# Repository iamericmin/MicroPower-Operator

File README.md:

# MicroPower-Operator
A simple SAMD21 dev board

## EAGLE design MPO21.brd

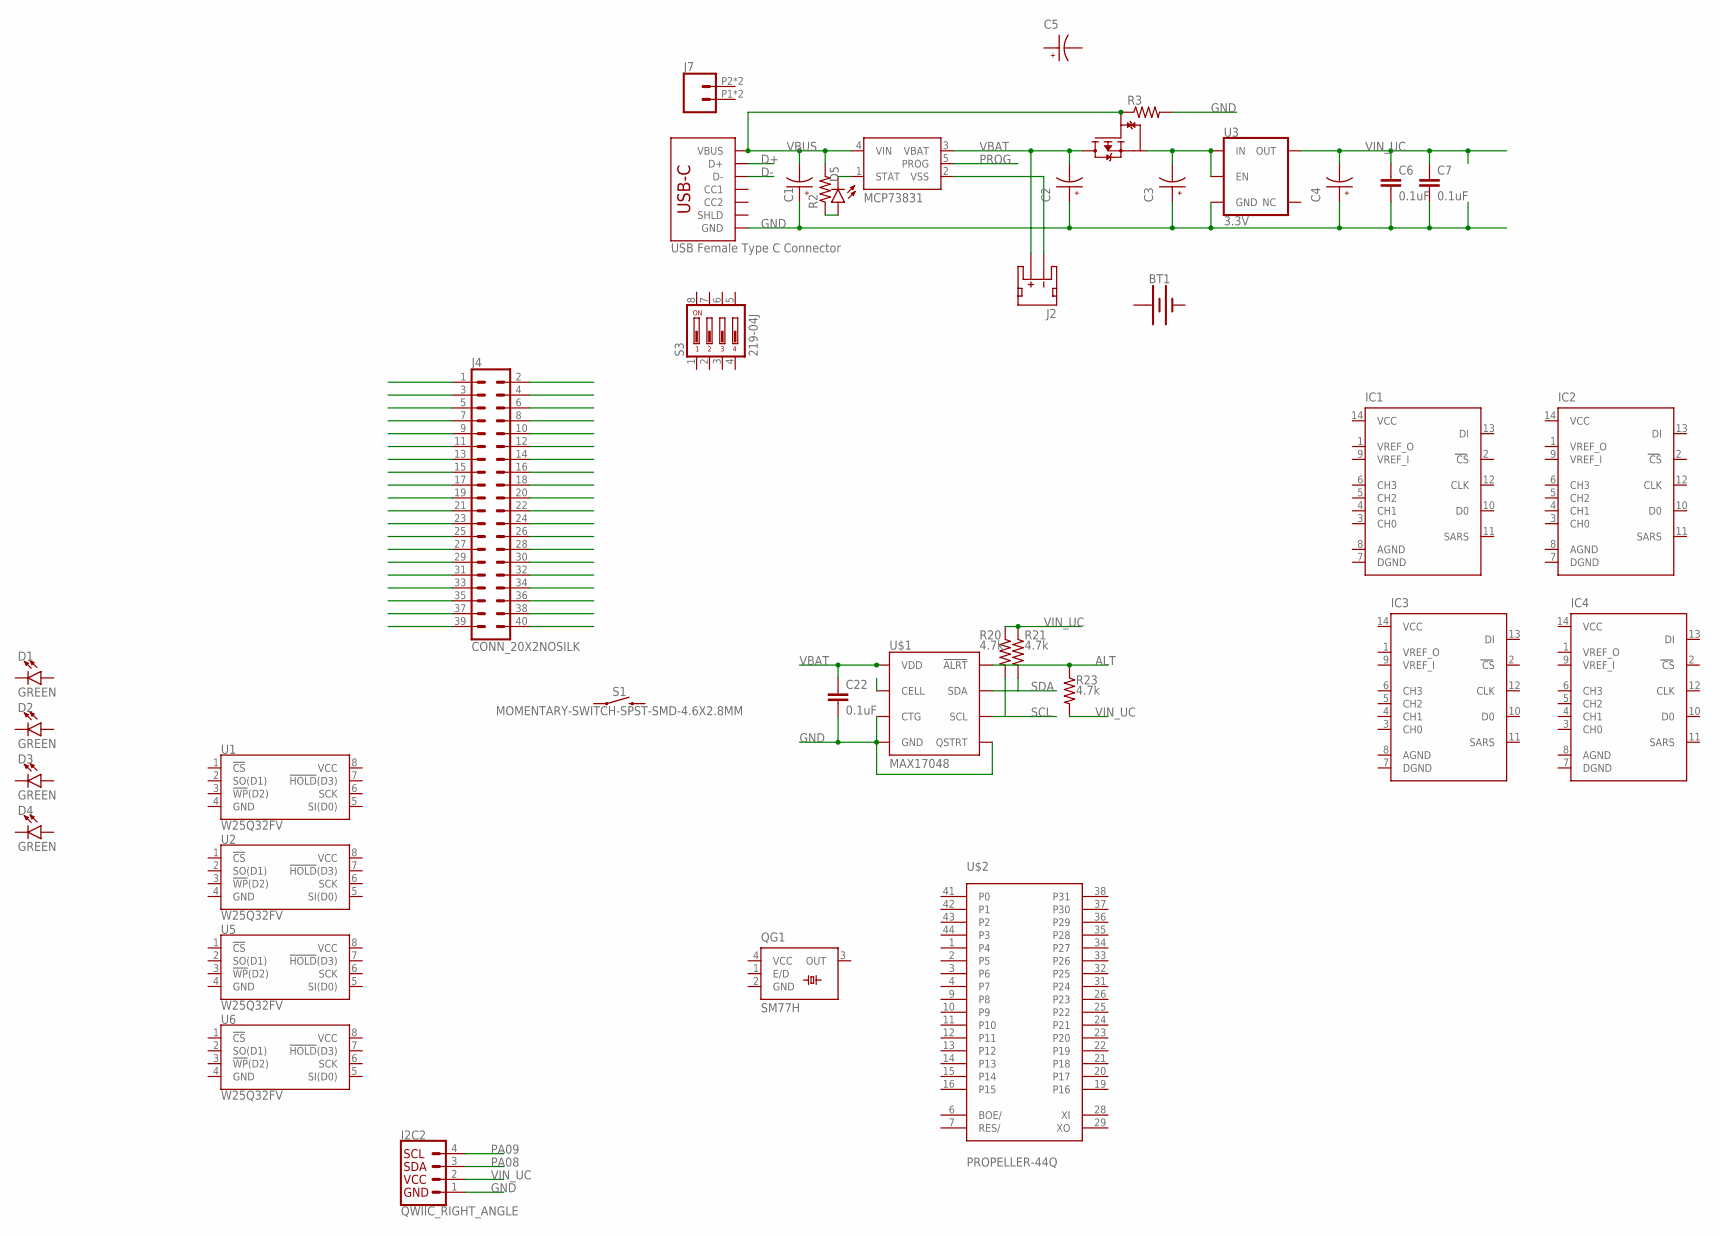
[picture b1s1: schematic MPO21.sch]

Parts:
BT1: BATTERY-20MM_SMD_4LEGS_OVERPASTE_INNER; BATTCON_20MM_4LEGS_OVERPASTE_INNER
C1, C2, C3, C4, C5: EEEFC1H1R0R; CAP_EEEFC1H1R0R
C6, C7, C22: 0.1uF; C0603
D1, D2, D3, D4, D5: GREEN; LED-1206
I2C2: QWIIC_RIGHT_ANGLE; JST04_1MM_RA
IC1, IC2, IC3, IC4: ADC08034D; SO14
J2: JST_2MM_MALE; JST-2-SMD
J4: CONN_20X2NOSILK; 2X20_NOSILK
J7: CONN_02SMALL_POKEHOME; 1X02_POKEHOME
J9: USB Female Type C Connector; USB-C-16P-4LAYER-ISOLATED
Q1: DMP1045U; SOT91P240X110-3N
QG1: SM77H
R2, R3: R-US_R0603; R0603
R20, R21, R23: 4.7k; R0603
S1: MOMENTARY-SWITCH-SPST-SMD-4.6X2.8MM; TACTILE_SWITCH_SMD_4.6X2.8MM
S3: 219-04J; CTS-219-04J
U1, U2, U5, U6: W25Q32FV; SOIC-8
U3: 3.3V; SOT23-5
U4: MCP73831; SOT23-5
U$1: MAX17048; DFN-8
U$2: PROPELLER-44Q; Q44

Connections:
+: BT1.1 (+)
-: BT1.2 (-)
AGND: IC1.8 (AGND), IC2.8 (AGND), IC3.8 (AGND), IC4.8 (AGND)
ALT: R23.1, U$1.P$5 (!ALRT)
D+: J9.A6 (D+), J9.B6 (D+)
D-: J9.A7 (D-), J9.B7 (D-)
DGND: IC1.7 (DGND), IC2.7 (DGND), IC3.7 (DGND), IC4.7 (DGND)
GND: C1.1, C2.1, C3.1, C4.1, C6.2, C7.2, C22.2, I2C2.1, J9.GND, J9.GND2 (GND), QG1.2 (GND), R3.2, U3.2 (GND), U$1.P$1 (CTG), U$1.P$4 (GND), U$1.P$6 (QSTRT), U$1.P$9 (GND)
unnamed: C3.2, Q1.2 (S), U3.1 (IN), U3.3 (EN)
unnamed: D5.C, U4.1 (STAT)
unnamed: J2.1 (-), U4.2 (VSS)
unnamed: D5.A, R2.1
PA01: J4.1
PA08: I2C2.3
PA09: I2C2.4
PROG: U4.5 (PROG)
SCL: R20.2, U$1.P$7 (SCL)
SDA: R21.2, U$1.P$8 (SDA)
VBAT: C2.2, C22.1, J2.2 (+), Q1.3 (D), U4.3 (VBAT), U$1.P$3 (VDD)
VBUS: C1.2, J9.VBUS1 (VBUS), J9.VBUS2 (VBUS), Q1.1 (G), R2.2, R3.1, U4.4 (VIN)
VCC: IC1.14 (VCC), IC2.14 (VCC), IC3.14 (VCC), IC4.14 (VCC), QG1.4 (VCC)
VDD: U$2.8 (VDD), U$2.18 (VDD), U$2.30 (VDD), U$2.40 (VDD)
VIN_UC: C4.2, C6.1, C7.1, I2C2.2, R20.1, R21.1, R23.2, U3.5 (OUT)
VSS: U$2.5 (VSS), U$2.17 (VSS), U$2.27 (VSS), U$2.39 (VSS)

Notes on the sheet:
R23
R20
R21

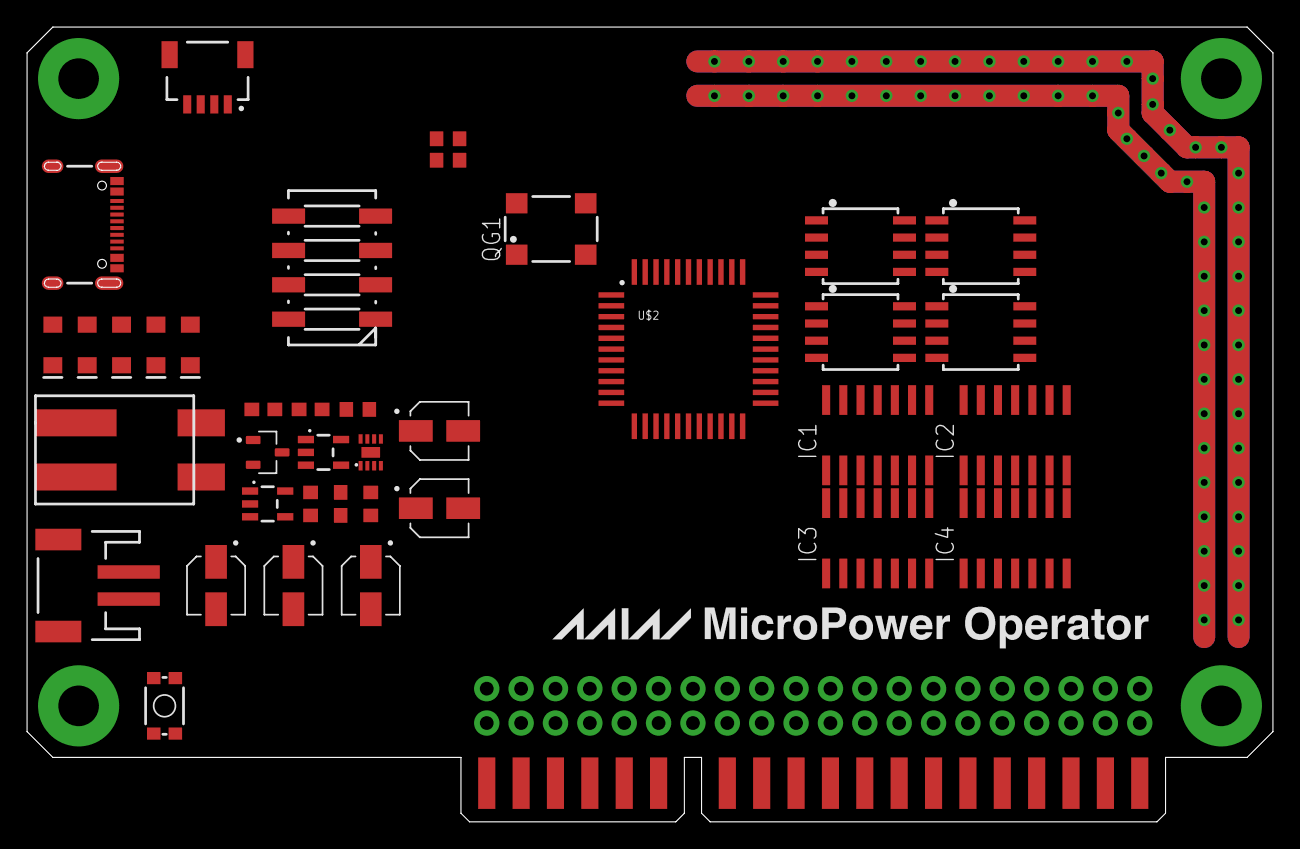
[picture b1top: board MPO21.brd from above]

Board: 2 copper layers, 92.1 x 58.7 mm, 40 parts (1 on the bottom side), 18 nets.

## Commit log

2023-04-09 first commit!
2023-04-15 propeller yo

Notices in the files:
parts and their libraries:
SparkFun-Connectors: Licensing: Creative Commons ShareAlike 4.0 International - https://creativecommons.org/licenses/by-sa/4.0
